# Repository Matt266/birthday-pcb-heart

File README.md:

# PCB Heart As Birthday Present

As birthday present for our mother my brother and I decided to create a heart-shaped PCB with a buzzer
to play "happy birthday" and LEDs to look pretty. It also should be powered by battery.

Two buttons allow cycling through brightness levels and to initiate the "happy birthday".  

<br><br>

## The Circuit

The exact partnumbers can be taken from the BOM and the KiCAD project. I decided to make use of a LiPo-battery for
the lower self discharge, higher capacity and possibility to recharge in comparison to regular batteries. 

A battery management ic controls charging and allowed me to add an usb connector as charging port. The PCB is also 
powered during charging. A P-Channel MOSFET protects the circuit for reverse polarity on the LiPo-Input. 

Two charge pumps step up the voltage to 5V. This made it Arduino compatible so I could more easily use an Arduino as
in circuit programmer. Also it kept the circuit smaller than inductor based boost-converter. This helped fitting all
components within the heart shape. 

The LEDs and the buzzer are controlled via N-Channel MOSFETs (one for all LEDs one for the buzzer) and connected to
PWM capable pins on the MCU.

To make it more Arduino capable and therefore ease programming for my brother I chose the classic Atmega328p as MCU. 
It was his first time programming something embedded and he did a great job! :)

## The Software

The Software was completely written by my brother (TODO: add Sketch to this repo).

## The Problems

As with all projetcs there are some things that I could have done better in the hindsight.

First of all I didn't include a switch on the PCB. I added one external switch between the LiPO-battery
and PCB afterwards but that isn't nearly as comfortable as having it included directly on the PCB.

The second problem are the charge pumps. While they get the job done they heave a massive quiescent current
and aren't really efficient.  Also running the MCU from a 5V supply voltage increased its power consumption in comparison to e.g. 3.3V.
As the voltage is stepped up the current drawn from the battery inceases even further.
This combination is responsble for a large standby current of 50mA. This massive quiescent current even makes it
unnecessary to consider putting the MCU sleeping. The current draw would remain high nonetheless.

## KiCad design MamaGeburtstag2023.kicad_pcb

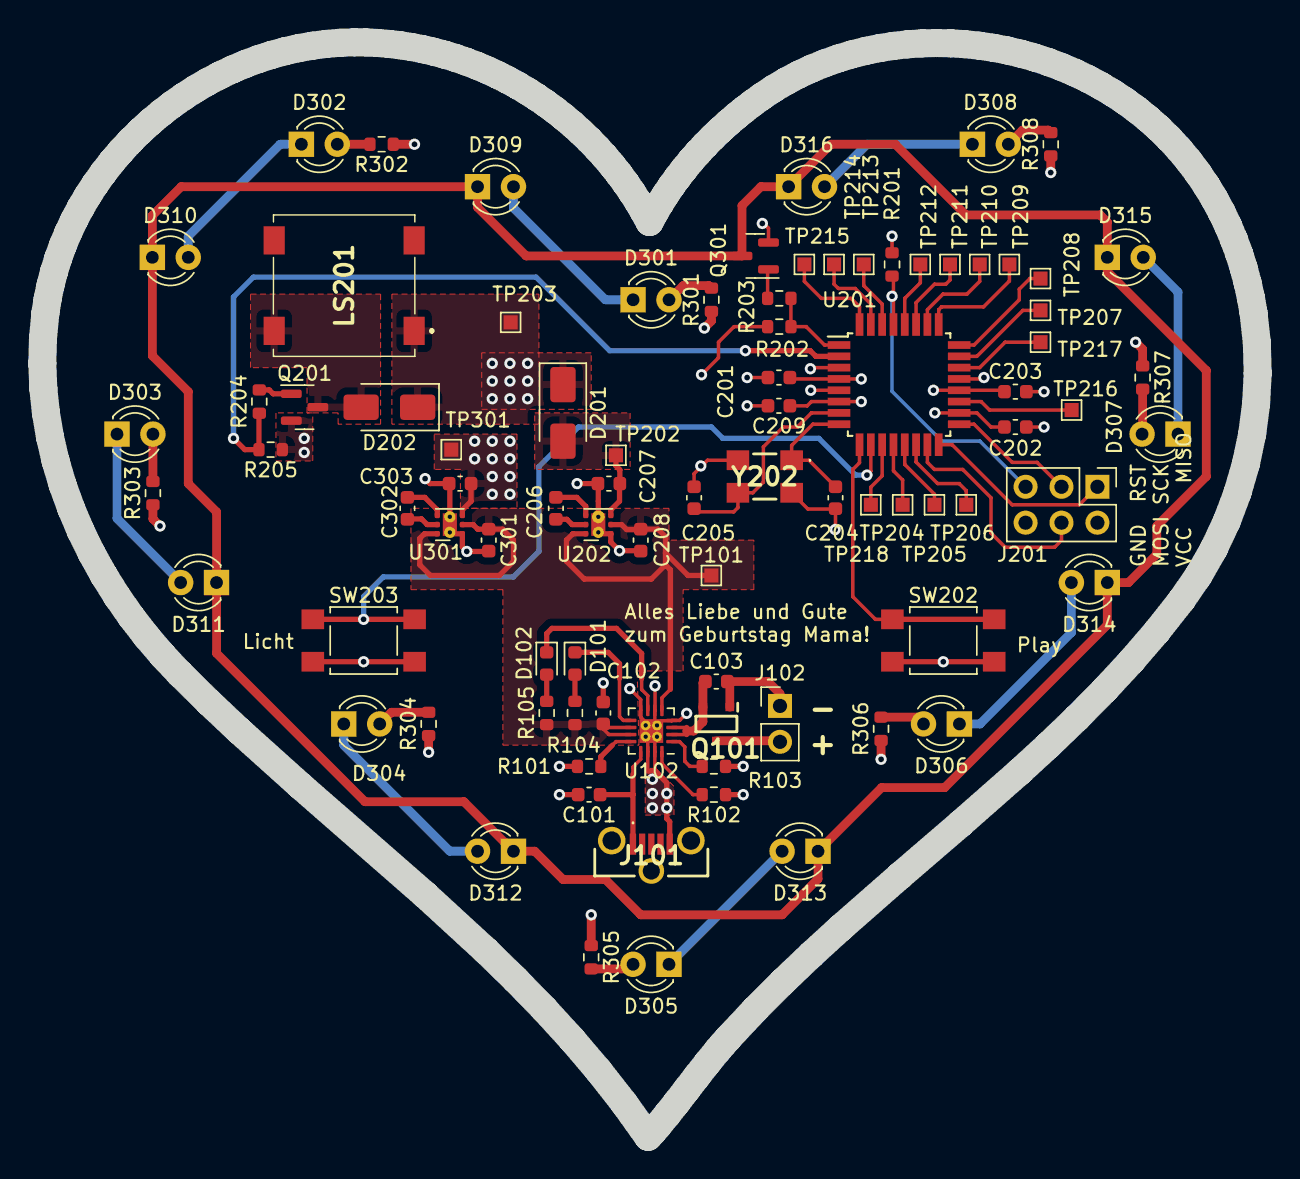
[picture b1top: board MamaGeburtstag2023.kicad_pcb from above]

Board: 4 copper layers, 86.0 x 77.4 mm, 86 parts (0 on the bottom side), 64 nets.

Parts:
C101, C102, C103, C206, C207, C208, C301, C302, C303: 4u7; C_0603_1608Metric
C201, C202, C203, C209: 100n; C_0603_1608Metric
C204, C205: 22p; C_0603_1608Metric
D101, D102: LED; LED_0603_1608Metric
D201, D202: B120-E3; D_SMA
D301, D302, D303, D304, D305, D306, D307, D308, D309, D310, D311, D312, D313, D314, D315, D316: LED; LED_D3.0mm
J101: GMCB05B11124H1EU
J102: Conn_01x02_Socket; PinHeader_1x02_P2.54mm_Vertical
J201: Conn_02x03_Odd_Even; PinHeader_2x03_P2.54mm_Vertical
LS201: CMT-1032-85-SMT-TR; CMT103285SMTTR
Q101: SSM3J358R,LF; SOTFL95P240X88-3N
Q201, Q301: 2N7002H; SOT-23
R101: 2k94; R_0603_1608Metric
R102: 4k32; R_0603_1608Metric
R103, R201, R202, R205: 10k; R_0603_1608Metric
R104, R105: 1k; R_0603_1608Metric
R203, R204, R301, R302, R303, R304, R305, R306, R307, R308: 200; R_0603_1608Metric
SW202, SW203: SW_SPST; SW_SPST_TL3305A
TP101, TP202, TP203, TP204, TP205, TP206, TP207, TP208, TP209, TP210, TP211, TP212, TP213, TP214, TP215, TP216, TP217, TP218, TP301: TestPoint; TestPoint_Pad_1.0x1.0mm
U102: BQ24230RGT; VQFN-16-1EP_3x3mm_P0.5mm_EP1.68x1.68mm_ThermalVias
U201: ATmega328P-A; TQFP-32_7x7mm_P0.8mm
U202, U301: TPS60151DRV; WSON-6-1EP_2x2mm_P0.65mm_EP1x1.6mm_ThermalVias
Y202: Crystal_GND24; 830030819

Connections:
+5V: C207.1, D201.2 (A), TP202.1, U202.3 (VOUT)
/CHG: D101.1 (K), U102.9 (CHG)
/Digital/ADC6: TP216.1, U201.19 (ADC6)
/Digital/ADC7: TP217.1, U201.22 (ADC7)
/Digital/PB0(ICP): TP204.1, U201.12 (PB0)
/Digital/PB1(OC1): TP205.1, U201.13 (PB1)
/Digital/PB2(SS): TP206.1, U201.14 (PB2)
/Digital/PB3(MOSI): J201.4, U201.15 (PB3)
/Digital/PB4(MISO): J201.1, U201.16 (PB4)
/Digital/PB5(SCK): J201.3, U201.17 (PB5)
/Digital/PC0(ADC0): TP207.1, U201.23 (PC0)
/Digital/PC1(ADC1): TP208.1, U201.24 (PC1)
/Digital/PC2(ADC2): TP209.1, U201.25 (PC2)
/Digital/PC3(ADC3): TP210.1, U201.26 (PC3)
/Digital/PC4(ADC4): TP211.1, U201.27 (PC4)
/Digital/PC5(ADC5): TP212.1, U201.28 (PC5)
/Digital/PC6(NRST): J201.5, R201.1, U201.29 (~RESET/PC6)
/Digital/PD0(RXD): TP213.1, U201.30 (PD0)
/Digital/PD1(TXD): TP214.1, U201.31 (PD1)
/Digital/PD2(INT0): TP215.1, U201.32 (PD2)
/Digital/PD3(INT1): R202.1, R203.1, U201.1 (PD3)
/Digital/PD4(T0): R204.1, R205.2, U201.2 (PD4)
/Digital/PD5(T1)\PLAY: SW202.1 (A), U201.9 (PD5)
/Digital/PD6(AIN0)\LIGHT: SW203.1 (A), U201.10 (PD6)
/Digital/PD7(AIN1): TP218.1, U201.11 (PD7)
/Digital/PWM_OUT: Q301.1 (G), R203.2
/PGOOD: D102.1 (K), U102.7 (PGOOD)
/VBAT: J102.2, Q101.3 (D)
/VBAT_POS: C103.1, Q101.2 (S), U102.2 (BAT), U102.3 (BAT)
/VBUS: C101.1, J101.1 (VBUS), U102.13 (IN)
/VIN: C102.1, C208.1, C301.1, R104.1, R105.1, TP101.1, U102.5 (EN2), U102.10 (OUT), U102.11 (OUT), U202.2 (VIN), U202.6 (ENA), U301.2 (VIN), U301.6 (ENA)
GND: C101.2, C102.2, C103.2, C201.2, C202.2, C203.2, C204.2, C205.2, C207.2, C208.2, C209.2, C301.2, C303.2, J101.5 (GND), J102.1, J201.6, Q101.1 (G), Q201.2 (S), Q301.2 (S), R101.1, R102.1, R103.1, R205.1, SW202.2 (B), SW203.2 (B), U102.4 (CE), U102.6 (EN1), U102.8 (VSS), U102.14 (TMR), U102.15 (TD), U102.17 (VSS), U201.3 (GND), U201.5 (GND), U201.21 (GND), U202.1 (GND), U202.7 (EP), U301.1 (GND), U301.7 (EP), Y202.2, Y202.4
unnamed: D101.2 (A), R104.2
unnamed: D102.2 (A), R105.2
unnamed: D202.2 (A), LS201.2 (-), Q201.3 (D)
unnamed: D301.2 (A), R301.2
unnamed: D301.1 (K), D309.2 (A)
unnamed: D302.2 (A), R302.2
unnamed: D302.1 (K), D310.2 (A)
unnamed: D303.2 (A), R303.2
unnamed: D303.1 (K), D311.2 (A)
unnamed: D304.2 (A), R304.2
unnamed: D304.1 (K), D312.2 (A)
unnamed: D305.2 (A), R305.2
unnamed: D305.1 (K), D313.2 (A)
unnamed: D306.2 (A), R306.2
unnamed: D306.1 (K), D314.2 (A)
unnamed: D307.2 (A), R307.2
unnamed: D307.1 (K), D315.2 (A)
unnamed: D308.2 (A), R308.2
unnamed: D308.1 (K), D316.2 (A)
unnamed: D309.1 (K), D310.1 (K), D311.1 (K), D312.1 (K), D313.1 (K), D314.1 (K), D315.1 (K), D316.1 (K), Q301.3 (D)
unnamed: Q201.1 (G), R204.2
unnamed: R101.2, U102.12 (ILIM)
unnamed: R102.2, U102.16 (ISET)
unnamed: R103.2, U102.1 (TS)
unnamed: C205.1, U201.7 (XTAL1/PB6), Y202.3
unnamed: C204.1, U201.8 (XTAL2/PB7), Y202.1
unnamed: C206.1, U202.4 (CP+)
unnamed: C206.2, U202.5 (CP-)
unnamed: C302.1, U301.4 (CP+)
unnamed: C302.2, U301.5 (CP-)
VCC: C201.1, C202.1, C203.1, C209.1, D201.1 (K), D202.1 (K), J201.2, LS201.1 (+), R201.2, R202.2, TP203.1, U201.4 (VCC), U201.6 (VCC), U201.18 (AVCC), U201.20 (AREF)
VD: C303.1, R301.1, R302.1, R303.1, R304.1, R305.1, R306.1, R307.1, R308.1, TP301.1, U301.3 (VOUT)
